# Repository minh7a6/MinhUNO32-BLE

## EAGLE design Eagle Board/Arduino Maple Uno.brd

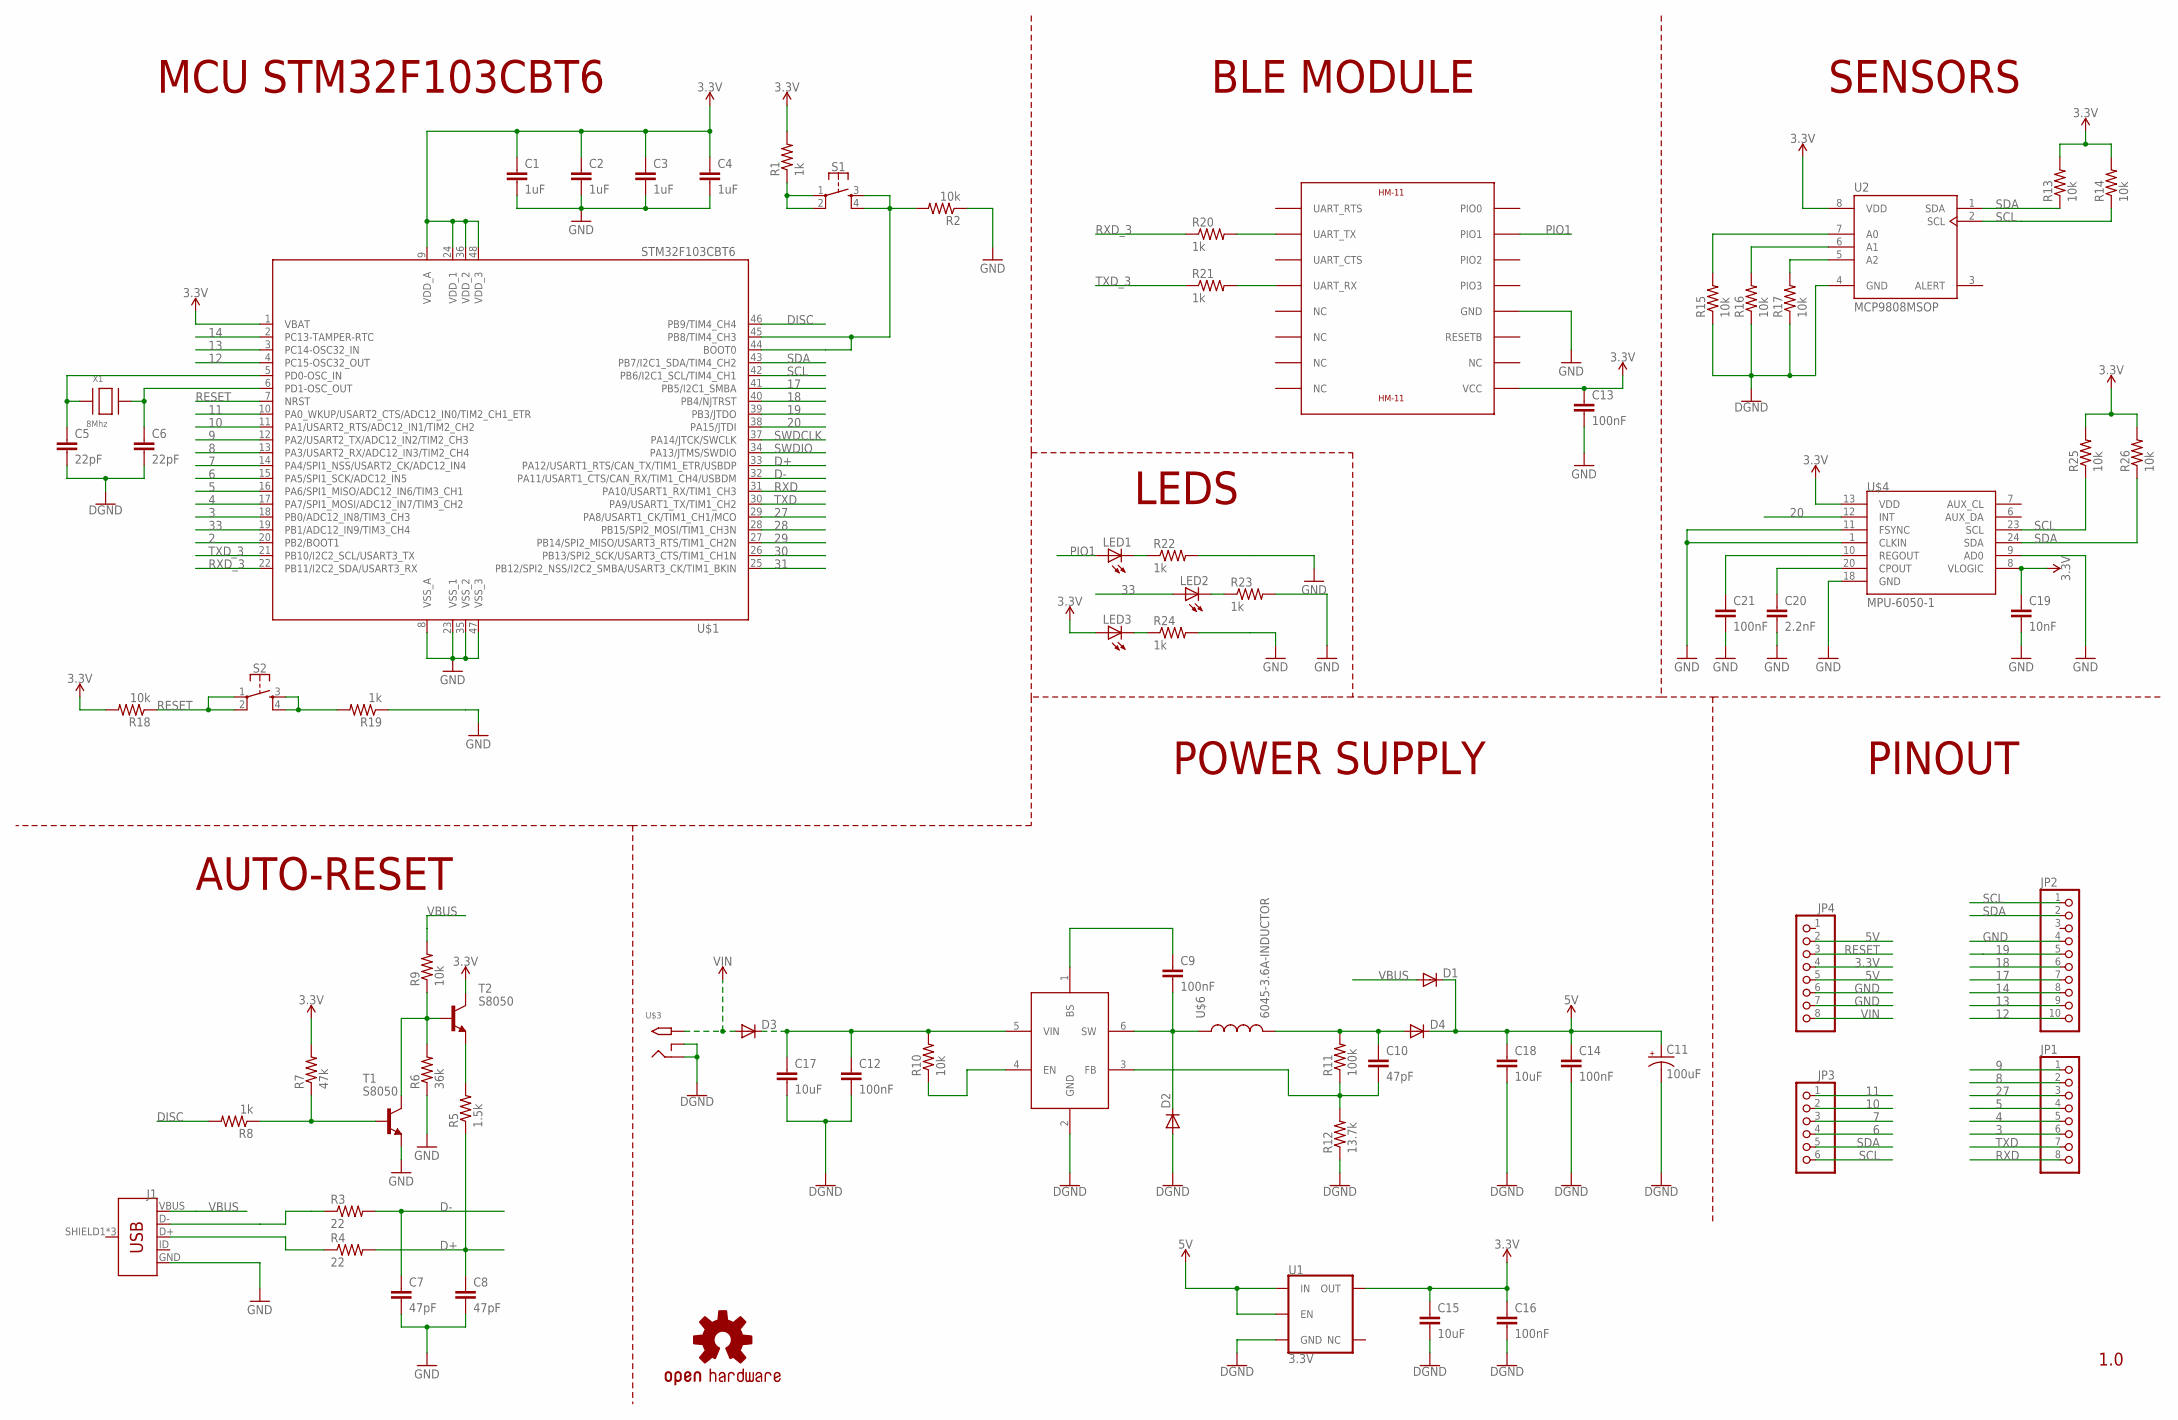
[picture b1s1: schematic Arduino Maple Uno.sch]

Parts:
C1, C2, C3, C4: 1uF; C0603
C5, C6: 22pF; C0603
C7, C8, C10: 47pF; C0603
C9, C12, C13, C14, C16, C21: 100nF; C0603
C11: 100uF; CT3528
C15, C18: 10uF; C0805
C17: 10uF; C1206
C19: 10nF; C0603
C20: 2.2nF; C0603
D1, D2, D3, D4: DIODE-DO-214AC; DO-214AC
J1: USB_MICRO-B_FEMALE-SMT; USB-B-MICRO-SMD
JP1, JP4: PINHD-1X8; 1X08
JP2: PINHD-1X10; 1X10
JP3: PINHD-1X6; 1X06
LED1, LED2, LED3: LEDCHIPLED_0603; CHIPLED_0603
LOGO1: OSHW-LOGOL-COPPER; OSHW-LOGO-L_COPPER
R1, R8, R19, R20, R21, R22, R23, R24: 1k; R0603
R2, R9, R10, R13, R14, R15, R16, R17, R18, R25, R26: 10k; R0603
R3, R4: 22; R0603
R5: 1.5k; R0603
R6: 36k; R0603
R7: 47k; R0603
R11: 100k; R0603
R12: 13.7k; R0603
S1, S2: MOMENTARY-SWITCH-SPST-2-SMD-5.2MM; TACTILE_SWITCH_SMD_5.2MM
T1, T2: S8050; SOT23
U1: 3.3V; SOT23-5
U2: MCP9808MSOP; MSOP-8
U$1: STM32F103CBT6; STM32_LQFP48
U$2: SY8113; TSOT23-6
U$3: 2.1MMJACKTHM; PJ-102A
U$4: MPU-6050-1; TESTING_QFN-24-4MM2
U$5: HM-11
U$6: 6045-3.6A-INDUCTOR; INDC6161X450
X1: 8Mhz; NX5032

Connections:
2: U$1.20 (PB2/BOOT1)
3: JP1.6, U$1.18 (PB0/ADC12_IN8/TIM3_CH3)
3.3V: C1.1, C2.1, C3.1, C4.1, C13.1, C15.1, C16.1, C19.1, JP4.4, LED3.A, R1.2, R7.2, R13.2, R14.2, R18.2, R25.2, R26.2, T2.3 (C), U1.5 (OUT), U2.8 (VDD), U$1.1 (VBAT), U$1.9 (VDD_A), U$1.24 (VDD_1), U$1.36 (VDD_2), U$1.48 (VDD_3), U$4.8 (VLOGIC), U$4.13 (VDD), U$5.VCC
4: JP1.5, U$1.17 (PA7/SPI1_MOSI/ADC12_IN7/TIM3_CH2)
5: JP1.4, U$1.16 (PA6/SPI1_MISO/ADC12_IN6/TIM3_CH1)
5V: C11.+, C14.1, C18.1, D1.C, D4.C, JP4.2, JP4.5, U1.1 (IN), U1.3 (EN)
6: JP3.4, U$1.15 (PA5/SPI1_SCK/ADC12_IN5)
7: JP3.3, U$1.14 (PA4/SPI1_NSS/USART2_CK/ADC12_IN4)
8: JP1.2, U$1.13 (PA3/USART2_RX/ADC12_IN3/TIM2_CH4)
9: JP1.1, U$1.12 (PA2/USART2_TX/ADC12_IN2/TIM2_CH3)
10: JP3.2, U$1.11 (PA1/USART2_RTS/ADC12_IN1/TIM2_CH2)
11: JP3.1, U$1.10 (PA0_WKUP/USART2_CTS/ADC12_IN0/TIM2_CH1_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)
12: JP2.10, U$1.4 (PC15-OSC32_OUT)
13: JP2.9, U$1.3 (PC14-OSC32_IN)
14: JP2.8, U$1.2 (PC13-TAMPER-RTC)
17: JP2.7, U$1.41 (PB5/I2C1_SMBA)
18: JP2.6, U$1.40 (PB4/NJTRST)
19: JP2.5, U$1.39 (PB3/JTDO)
20: U$1.38 (PA15/JTDI), U$4.12 (INT)
27: JP1.3, U$1.29 (PA8/USART1_CK/TIM1_CH1/MCO)
28: U$1.28 (PB15/SPI2_MOSI/TIM1_CH3N)
29: U$1.27 (PB14/SPI2_MISO/USART3_RTS/TIM1_CH2N)
30: U$1.26 (PB13/SPI2_SCK/USART3_CTS/TIM1_CH1N)
31: U$1.25 (PB12/SPI2_NSS/I2C2_SMBA/USART3_CK/TIM1_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)
33: LED2.A, U$1.19 (PB1/ADC12_IN9/TIM3_CH4)
D+: C8.1, R4.2, R5.1, U$1.33 (PA12/USART1_RTS/CAN_TX/TIM1_ETR/USBDP)
D-: C7.1, R3.2, U$1.32 (PA11/USART1_CTS/CAN_RX/TIM1_CH4/USBDM)
DISC: R8.2, U$1.46 (PB9/TIM4_CH4)
GND: C1.2, C2.2, C3.2, C4.2, C5.2, C6.2, C7.2, C8.2, C11.-, C12.2, C13.2, C14.2, C15.2, C16.2, C17.2, C18.2, C19.2, C20.2, C21.2, D2.A, J1.GND, JP2.4, JP4.6, JP4.7, R2.1, R6.1, R12.1, R15.1, R16.1, R17.1, R19.1, R22.2, R23.2, R24.2, T1.2 (E), U1.2 (GND), U2.4 (GND), U$1.8 (VSS_A), U$1.23 (VSS_1), U$1.35 (VSS_2), U$1.47 (VSS_3), U$2.2 (GND), U$3.RING, U$3.RING_SW, U$4.1 (CLKIN), U$4.9 (AD0), U$4.11 (FSYNC), U$4.18 (GND), U$5.GND
unnamed: R1.1, S1.1, S1.2
unnamed: C5.1, U$1.5 (PD0-OSC_IN), X1.P$1
unnamed: C6.1, U$1.6 (PD1-OSC_OUT), X1.P$2
unnamed: R2.2, S1.3, S1.4, U$1.44 (BOOT0), U$1.45 (PB8/TIM4_CH3)
unnamed: C9.2, D2.C, U$2.6 (SW), U$6.1
unnamed: J1.D-, R3.1
unnamed: J1.D+, R4.1
unnamed: R5.2, T2.2 (E)
unnamed: R6.2, R9.1, T1.3 (C), T2.1 (B)
unnamed: R7.1, R8.1, T1.1 (B)
unnamed: R19.2, S2.3, S2.4
unnamed: LED1.C, R22.1
unnamed: R15.2, U2.7 (A0)
unnamed: R10.1, U$2.4 (EN)
unnamed: C9.1, U$2.1 (BS)
unnamed: C10.2, R11.1, R12.2, U$2.3 (FB)
unnamed: R16.2, U2.6 (A1)
unnamed: R17.2, U2.5 (A2)
unnamed: R20.2, U$5.UART_TX
unnamed: C12.1, C17.1, D3.C, R10.2, U$2.5 (VIN)
unnamed: R21.2, U$5.UART_RX
unnamed: LED2.C, R23.1
unnamed: LED3.C, R24.1
unnamed: C10.1, D4.A, R11.2, U$6.2
unnamed: C21.1, U$4.10 (REGOUT)
unnamed: C20.1, U$4.20 (CPOUT)
PIO1: LED1.A, U$5.PIO1
RESET: JP4.3, R18.1, S2.1, S2.2, U$1.7 (NRST)
RXD: JP1.8, U$1.31 (PA10/USART1_RX/TIM1_CH3)
RXD_3: R20.1, U$1.22 (PB11/I2C2_SDA/USART3_RX)
SCL: JP2.1, JP3.6, R14.1, R25.1, U2.2 (SCL), U$1.42 (PB6/I2C1_SCL/TIM4_CH1), U$4.23 (SCL)
SDA: JP2.2, JP3.5, R13.1, R26.1, U2.1 (SDA), U$1.43 (PB7/I2C1_SDA/TIM4_CH2), U$4.24 (SDA)
SWDCLK: U$1.37 (PA14/JTCK/SWCLK)
SWDIO: U$1.34 (PA13/JTMS/SWDIO)
TXD: JP1.7, U$1.30 (PA9/USART1_TX/TIM1_CH2)
TXD_3: R21.1, U$1.21 (PB10/I2C2_SCL/USART3_TX)
VBUS: D1.A, J1.VBUS, R9.2
VIN: D3.A, JP4.8, U$3.TIP

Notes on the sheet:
MCU STM32F103CBT6
LEDS
BLE MODULE
SENSORS
PINOUT
POWER SUPPLY
AUTO-RESET
1.0

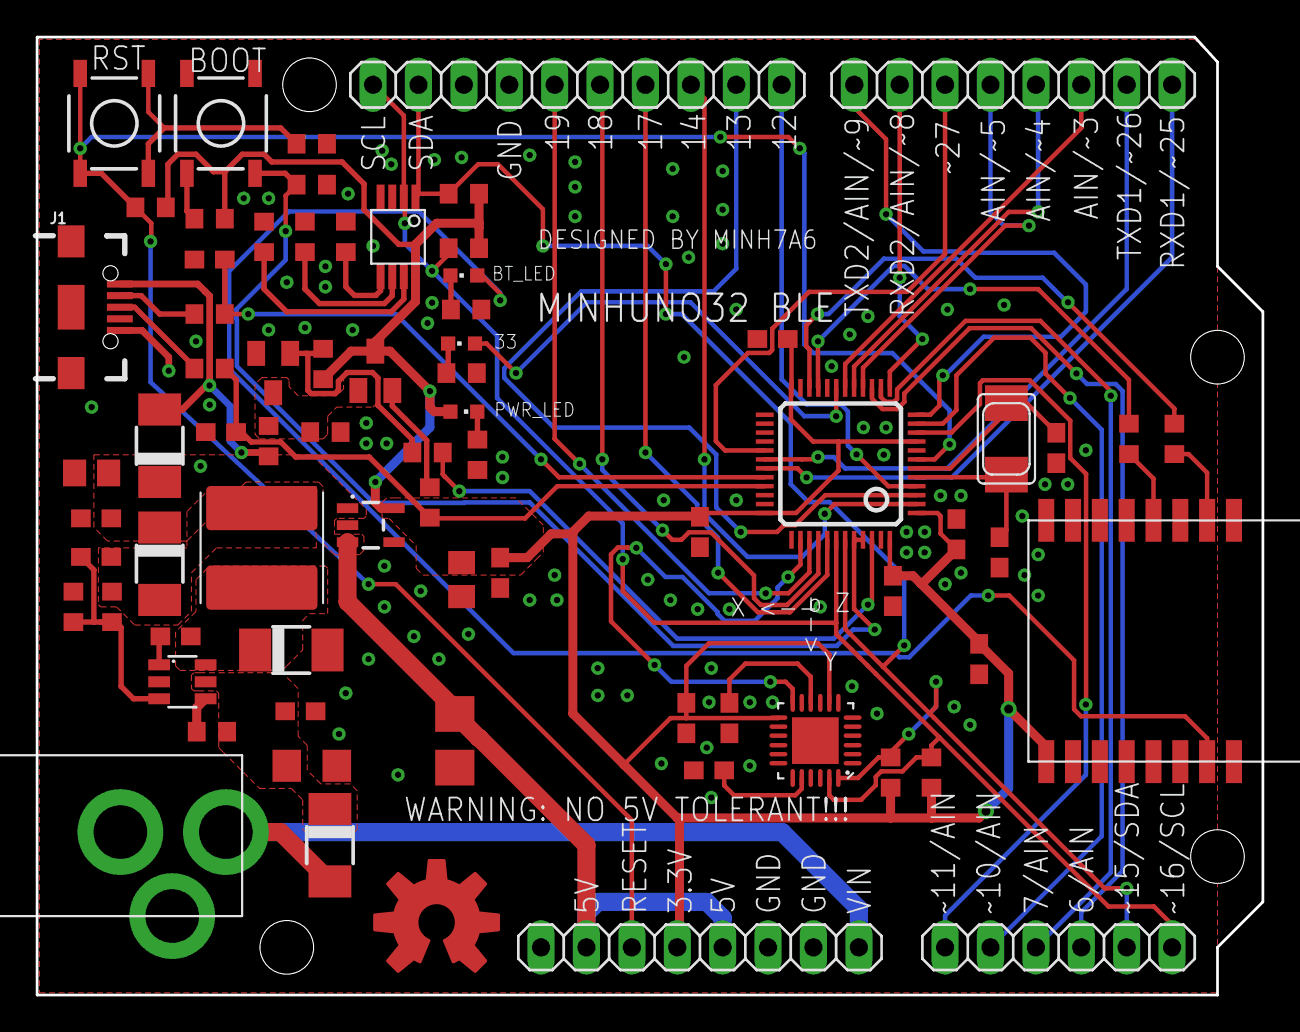
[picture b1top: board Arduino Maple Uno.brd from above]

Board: 2 copper layers, 68.6 x 53.6 mm, 73 parts (0 on the bottom side), 60 nets.

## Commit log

2018-12-15 Added Board Definition
2018-12-15 Added Hardware
2018-12-15 Change image to higher resolution
2018-12-15 minor changes
2018-12-27 changes in design
2018-12-27 added MPU6050 IMU
2019-01-10 Prepare for board manager
2019-01-10 board manager file
2019-01-10 changes1
2019-01-10 test

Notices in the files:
parts and their libraries:
SparkFun-Connectors: Licensing: Creative Commons ShareAlike 4.0 International - https://creativecommons.org/licenses/by-sa/4.0
